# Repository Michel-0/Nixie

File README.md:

# Nixie
All you need to know to build a cold cathode tube display clock

## Concept
There are many different concepts with different features possible.

**The concept of this repository:**

* Controlled by a Raspberry Pi Pico.
* Designed for Gazotron IN-14 tubes, may be adapted for others easily.  
E.g. IN-8 and IN-8-2 should be compatible without any change.
* Makes use of the right comma of the tube, but not the left one.  
However the tube socket PCB connects both to the main PCB.
* Prepared for IN-3 tubes as colon dots.
* Tube voltage step-up boost converter not inclued on this PCB.  
Instead the layout has free space and connectors for it.
* For syncing / keeping time there are 3 options (multiple combinable)
  * **Option A:** A DCF77 (77,5 kHz) radio clock receiver to get the time once powered on.  
Smallest, cheapest and easiest option, but unstable because of many high frequent other things on the board.
  * **Option B:** A RTC (real-time clock) with battery.  
Requires manual time input once or combination with another option.
  * **Option C:** A GPS receiver to get the GPS time once powered on.  
Seems a bit like a overkill, but actually a valid option. Size and costs similar as A & B together.
* Tube driver based on MPSA42 transistors controlled by MCP23008 & MCP23017 connected by I²C to the pico.  
No historical sovjet ICs necessary
* Supplied by external 12V DC.
* Provides connectors for 5V RGB LEDs (e.g. WS2812B).

## Repository
### KiCAD project
Folder `NTC` contains:
* **Main**:  
Clock schematic and PCB
* **Socket**:  
IN-14 schematic and PCB
* **Footprints**  
Project library called `Nixie` containing all used footprints
* **Symbols**  
Project library called `Nixie` containig an additional symbol
* **CAD**  
3D models that weren't included in the default library

### C++ VSCode project
Pico software may or may not be added to this repository in near future.

## Datasheets
[IN-14 Manual](../../wiki/IN‐14-Manuals)

## Dimensioning
[IN-14 Calculations](../../wiki/IN‐14-Calculations)

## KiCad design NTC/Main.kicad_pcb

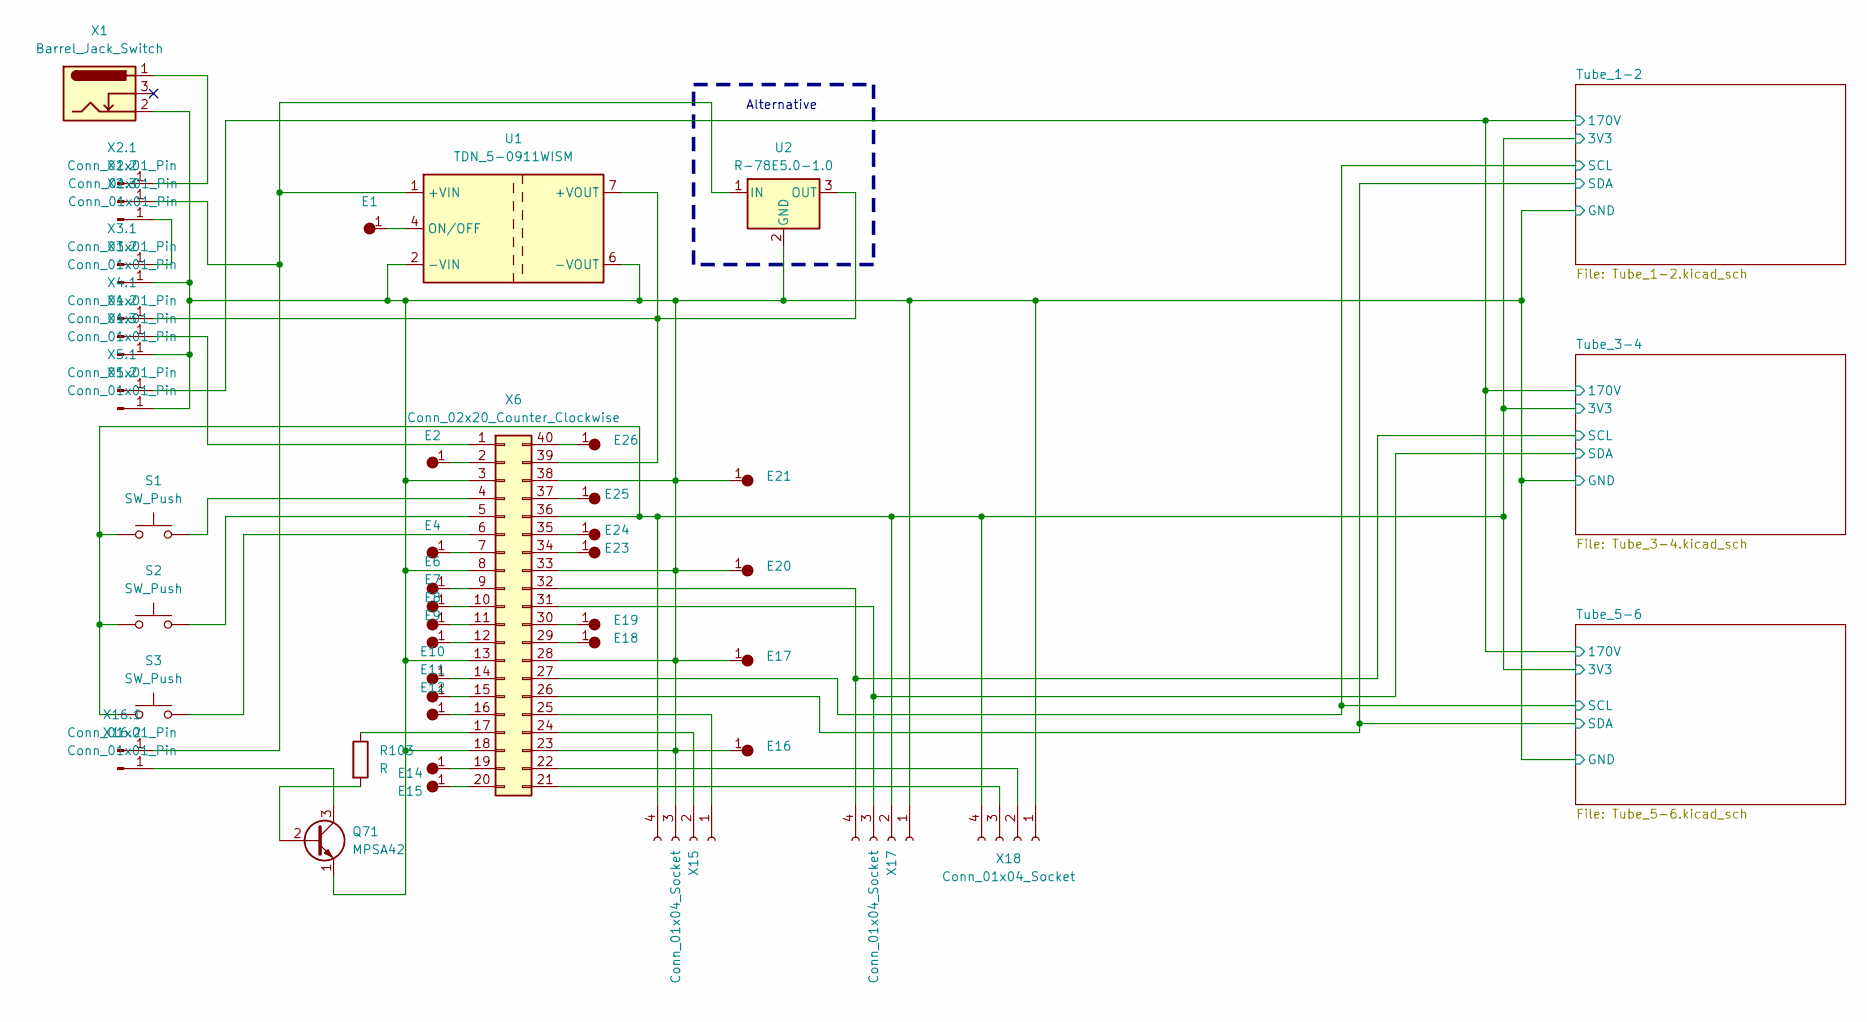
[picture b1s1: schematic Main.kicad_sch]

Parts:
E1, E2, E4, E6, E7, E8, E9, E10, E11, E12, E14, E15, E16, E17, E18, E19, E20, E21, E23, E24, E25, E26: SingleHole
Q71: MPSA42; MPSA-42
R103: R; Resistor-a
S1, S2, S3: SW_Push; Button
U1: TDN_5-0911WISM; DCDC_12V-5V-3W
U2: R-78E5.0-1.0; DCDC_12V-5V-5W
X1: Barrel_Jack_Switch; Socket_5-5
X2.1, X2.2, X2.3, X3.1, X3.2, X4.1, X4.2, X4.3, X5.1, X5.2, X16.1, X16.2: Conn_01x01_Pin; Pin_D1.0mm_L10.0mm
X6: Conn_02x20_Counter_Clockwise; Pinbar_1-20-f
X15: Conn_01x04_Socket; Pinbar_1-4-f-b
X17: Conn_01x04_Socket; Pinbar_1-4-f-c
X18: Conn_01x04_Socket; Pinbar_1-4-f-d

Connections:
/Tube_1-2/3V3: S1.1, S2.1, S3.1, X6.36, X15.4, X17.2, X18.4; also elsewhere on the board
/Tube_1-2/170V: X5.1.1; also elsewhere on the board
/Tube_1-2/GND: E16.1, E17.1, E20.1, E21.1, Q71.1 (E), U1.2 (-VIN), U1.6 (-VOUT), U2.2 (GND), X1.2, X3.2.1, X4.3.1, X5.2.1, X6.3, X6.8, X6.13, X6.18, X6.23, X6.28, X6.33, X6.38, X15.3, X17.1, X18.1; also elsewhere on the board
/Tube_1-2/SCL: X6.27; also elsewhere on the board
/Tube_1-2/SDA: X6.26; also elsewhere on the board
/Tube_3-4/SCL: X6.32, X17.4; also elsewhere on the board
/Tube_3-4/SDA: X6.31, X17.3; also elsewhere on the board
unnamed: Q71.2 (B), R103.2
unnamed: Q71.3 (C), X16.2.1
unnamed: U1.1 (+VIN), U2.1 (IN), X2.2.1, X16.1.1
unnamed: U1.7 (+VOUT), U2.3 (OUT), X4.1.1, X6.39
unnamed: E1.1, U1.4 (ON/OFF)
unnamed: X1.1, X2.1.1
unnamed: X2.3.1, X3.1.1
unnamed: X4.2.1, X6.1
unnamed: E2.1, X6.2
unnamed: S1.2, X6.4
unnamed: S2.2, X6.5
unnamed: S3.2, X6.6
unnamed: E4.1, X6.7
unnamed: E6.1, X6.9
unnamed: E7.1, X6.10
unnamed: E8.1, X6.11
unnamed: E9.1, X6.12
unnamed: E10.1, X6.14
unnamed: E11.1, X6.15
unnamed: E12.1, X6.16
unnamed: R103.1, X6.17
unnamed: E14.1, X6.19
unnamed: E15.1, X6.20
unnamed: E18.1, X6.29
unnamed: E19.1, X6.30
unnamed: E23.1, X6.34
unnamed: E24.1, X6.35
unnamed: E25.1, X6.37
unnamed: E26.1, X6.40
unnamed: X6.25, X15.1
unnamed: X6.24, X15.2
unnamed: X6.22, X18.2
unnamed: X6.21, X18.3

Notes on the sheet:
Alternative

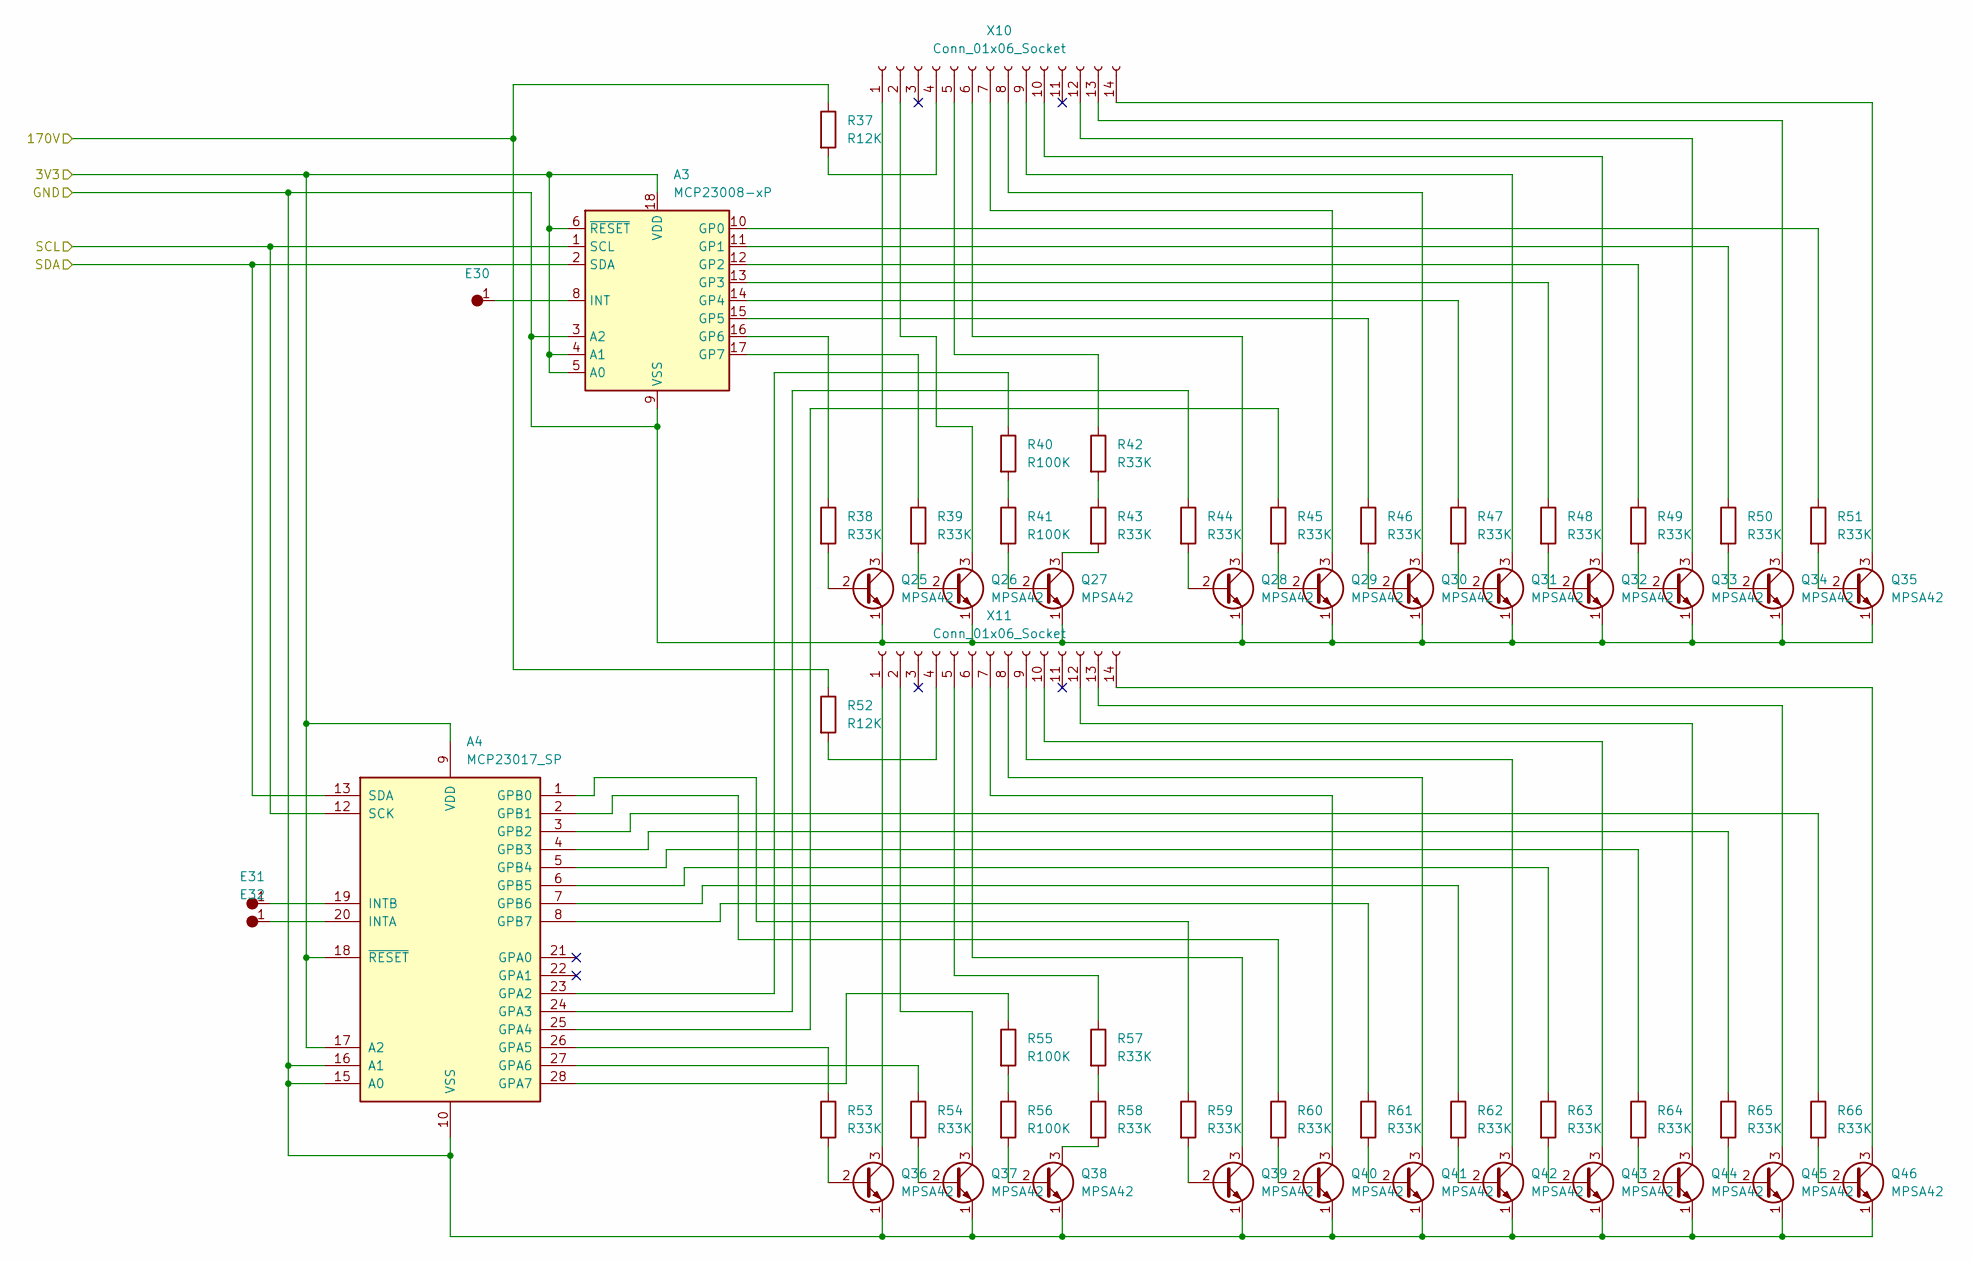
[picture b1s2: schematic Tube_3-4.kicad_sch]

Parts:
A3: MCP23008-xP; DIP-18_IC+Socket
A4: MCP23017_SP; DIP-28_IC+Socket
E30, E31, E32: SingleHole
Q25, Q26, Q27, Q28, Q29, Q30, Q31, Q32, Q33, Q34, Q35, Q36, Q37, Q38, Q39, Q40, Q41, Q42, Q43, Q44, Q45, Q46: MPSA42; MPSA-42
R37, R52: R12K; Resistor-a
R38, R39, R42, R43, R44, R45, R46, R47, R48, R49, R50, R51, R53, R54, R57, R58, R59, R60, R61, R62, R63, R64, R65, R66: R33K; Resistor-a
R40, R41, R55, R56: R100K; Resistor-a
X10, X11: Conn_01x06_Socket; Pinbar_4-14-f

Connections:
/Tube_1-2/3V3: A3.4 (A1), A3.5 (A0), A3.6 (~RESET), A3.18 (VDD), A4.9 (VDD), A4.17 (A2), A4.18 (~RESET); also elsewhere on the board
/Tube_1-2/170V: R37.1, R52.1; also elsewhere on the board
/Tube_1-2/GND: A3.3 (A2), A3.9 (VSS), A4.10 (VSS), A4.15 (A0), A4.16 (A1), Q25.1 (E), Q26.1 (E), Q27.1 (E), Q28.1 (E), Q29.1 (E), Q30.1 (E), Q31.1 (E), Q32.1 (E), Q33.1 (E), Q34.1 (E), Q35.1 (E), Q36.1 (E), Q37.1 (E), Q38.1 (E), Q39.1 (E), Q40.1 (E), Q41.1 (E), Q42.1 (E), Q43.1 (E), Q44.1 (E), Q45.1 (E), Q46.1 (E); also elsewhere on the board
/Tube_3-4/SCL: A3.1 (SCL), A4.12 (SCK); also elsewhere on the board
/Tube_3-4/SDA: A3.2 (SDA), A4.13 (SDA); also elsewhere on the board
unnamed: A3.10 (GP0), R51.1
unnamed: A3.11 (GP1), R50.1
unnamed: A3.12 (GP2), R49.1
unnamed: A3.13 (GP3), R48.1
unnamed: A3.14 (GP4), R47.1
unnamed: A3.15 (GP5), R46.1
unnamed: A3.16 (GP6), R38.1
unnamed: A3.17 (GP7), R39.1
unnamed: A3.8 (INT), E30.1
unnamed: A4.23 (GPA2), R40.1
unnamed: A4.24 (GPA3), R44.1
unnamed: A4.25 (GPA4), R45.1
unnamed: A4.26 (GPA5), R53.1
unnamed: A4.27 (GPA6), R54.1
unnamed: A4.28 (GPA7), R55.1
unnamed: A4.1 (GPB0), R59.1
unnamed: A4.2 (GPB1), R60.1
unnamed: A4.3 (GPB2), R66.1
unnamed: A4.4 (GPB3), R65.1
unnamed: A4.5 (GPB4), R64.1
unnamed: A4.6 (GPB5), R63.1
unnamed: A4.7 (GPB6), R62.1
unnamed: A4.8 (GPB7), R61.1
unnamed: A4.20 (INTA), E32.1
unnamed: A4.19 (INTB), E31.1
unnamed: Q25.2 (B), R38.2
unnamed: Q25.3 (C), X10.1
unnamed: Q26.2 (B), R39.2
unnamed: Q26.3 (C), X10.2
unnamed: Q27.2 (B), R41.2
unnamed: Q27.3 (C), R43.2
unnamed: Q28.2 (B), R44.2
unnamed: Q28.3 (C), X10.6
unnamed: Q29.2 (B), R45.2
unnamed: Q29.3 (C), X10.7
unnamed: Q30.2 (B), R46.2
unnamed: Q30.3 (C), X10.8
unnamed: Q31.2 (B), R47.2
unnamed: Q31.3 (C), X10.9
unnamed: Q32.2 (B), R48.2
unnamed: Q32.3 (C), X10.10
unnamed: Q33.2 (B), R49.2
unnamed: Q33.3 (C), X10.12
unnamed: Q34.2 (B), R50.2
unnamed: Q34.3 (C), X10.13
unnamed: Q35.2 (B), R51.2
unnamed: Q35.3 (C), X10.14
unnamed: Q36.2 (B), R53.2
unnamed: Q36.3 (C), X11.1
unnamed: Q37.2 (B), R54.2
unnamed: Q37.3 (C), X11.2
unnamed: Q38.2 (B), R56.2
unnamed: Q38.3 (C), R58.2
unnamed: Q39.2 (B), R59.2
unnamed: Q39.3 (C), X11.6
unnamed: Q40.2 (B), R60.2
unnamed: Q40.3 (C), X11.7
unnamed: Q41.2 (B), R61.2
unnamed: Q41.3 (C), X11.8
unnamed: Q42.2 (B), R62.2
unnamed: Q42.3 (C), X11.9
unnamed: Q43.2 (B), R63.2
unnamed: Q43.3 (C), X11.10
unnamed: Q44.2 (B), R64.2
unnamed: Q44.3 (C), X11.12
unnamed: Q45.2 (B), R65.2
unnamed: Q45.3 (C), X11.13
unnamed: Q46.2 (B), R66.2
unnamed: Q46.3 (C), X11.14
unnamed: R40.2, R41.1
unnamed: R42.2, R43.1
unnamed: R55.2, R56.1
unnamed: R57.2, R58.1
unnamed: R37.2, X10.4
unnamed: R42.1, X10.5
unnamed: R52.2, X11.4
unnamed: R57.1, X11.5

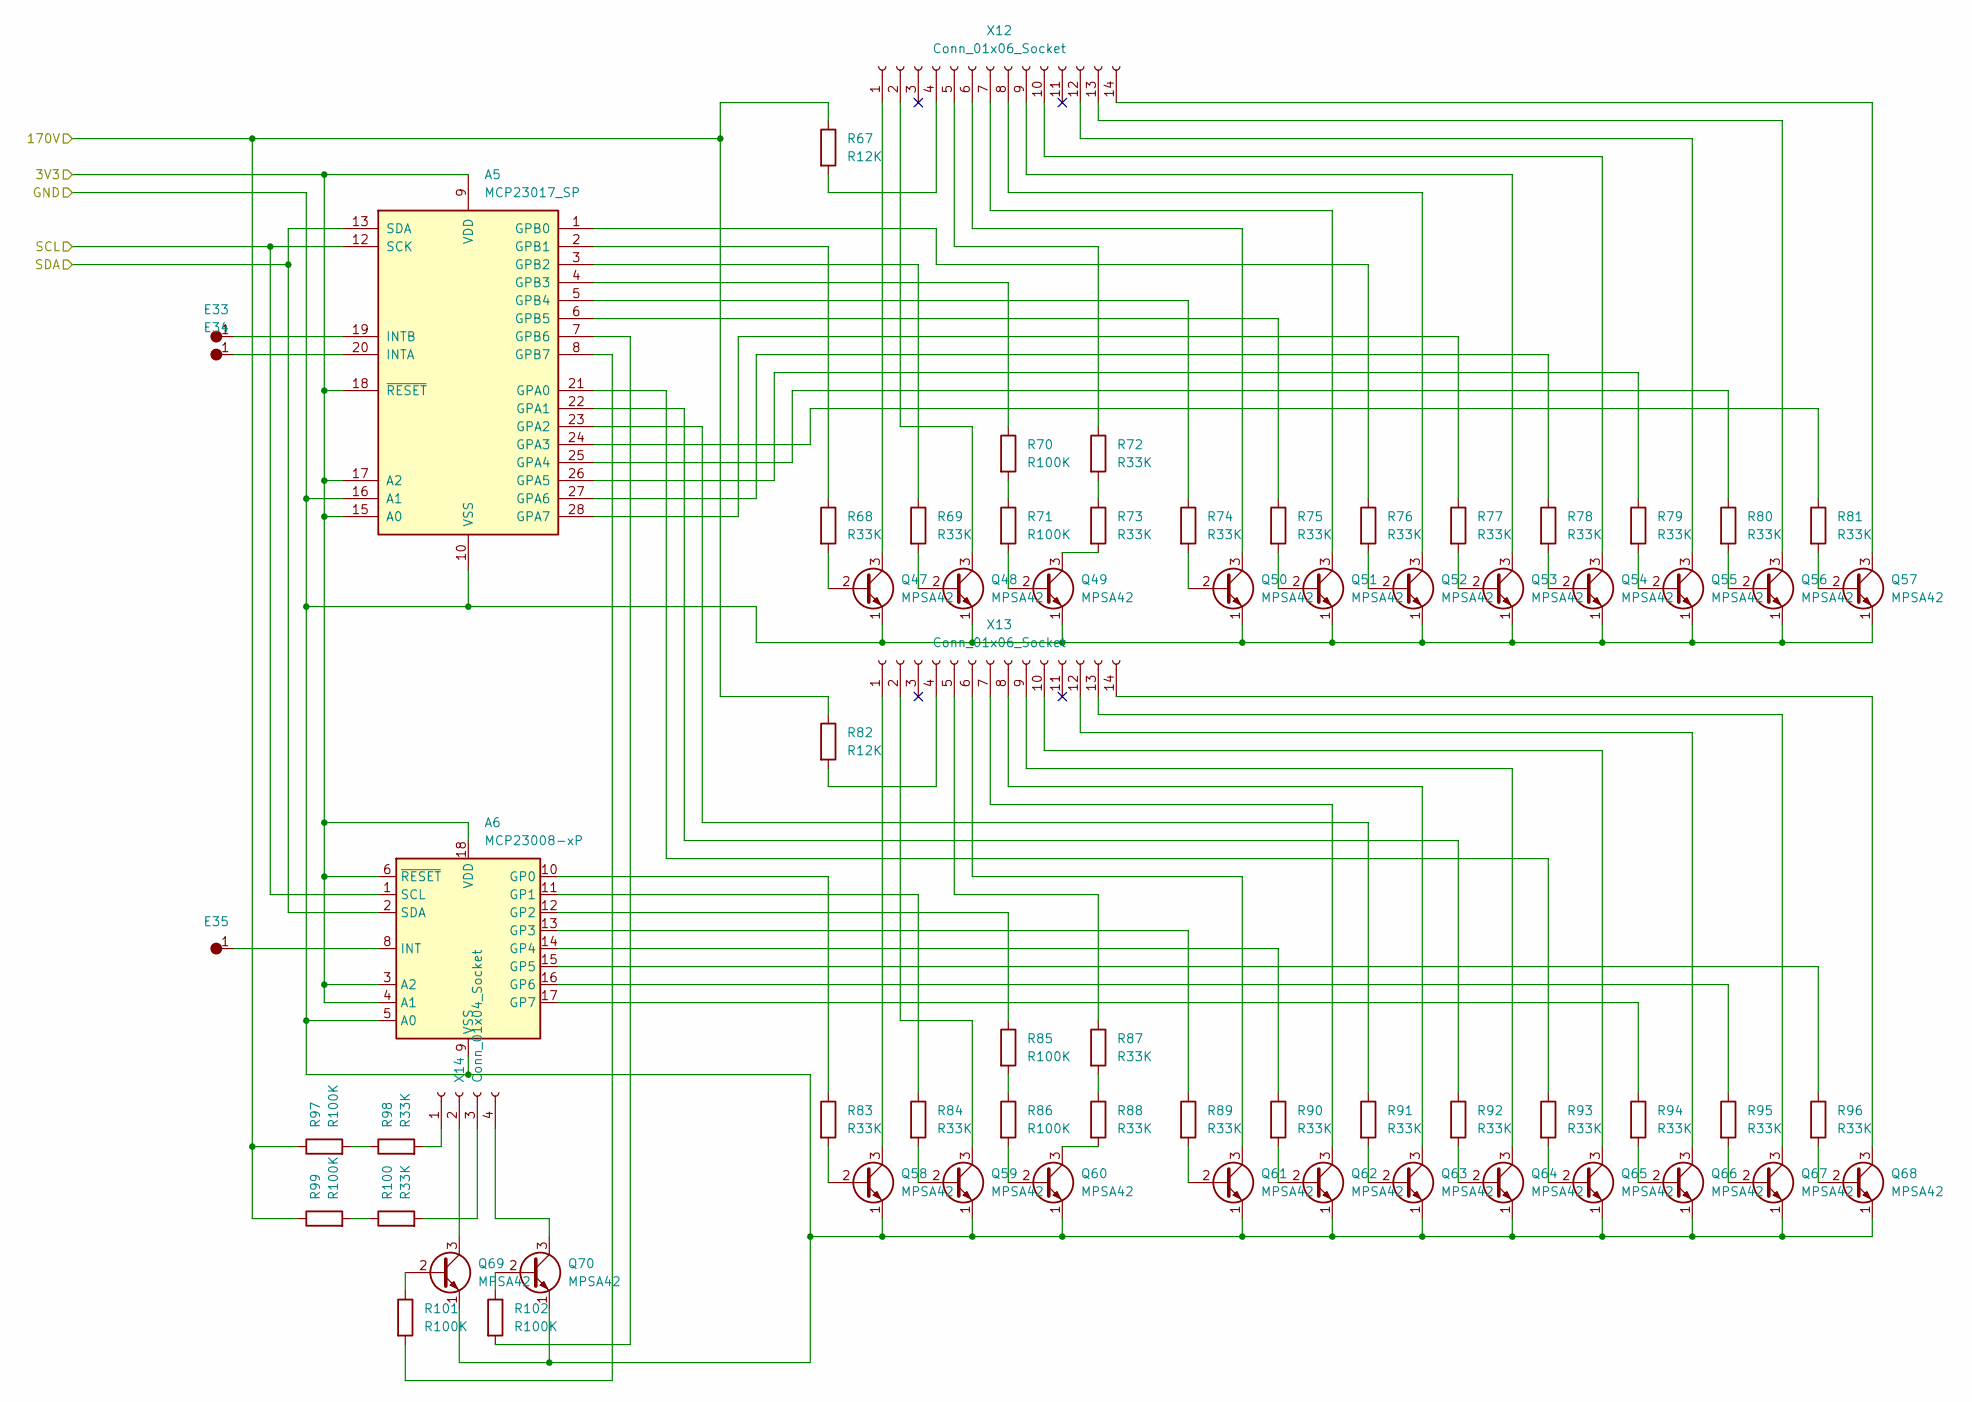
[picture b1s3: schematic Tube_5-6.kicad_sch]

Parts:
A5: MCP23017_SP; DIP-28_IC+Socket
A6: MCP23008-xP; DIP-18_IC+Socket
E33, E34, E35: SingleHole
Q47, Q48, Q49, Q50, Q51, Q52, Q53, Q54, Q55, Q56, Q57, Q58, Q59, Q60, Q61, Q62, Q63, Q64, Q65, Q66, Q67, Q68, Q69, Q70: MPSA42; MPSA-42
R67, R82: R12K; Resistor-a
R68, R69, R72, R73, R74, R75, R76, R77, R78, R79, R80, R81, R83, R84, R87, R88, R89, R90, R91, R92, R93, R94, R95, R96, R98, R100: R33K; Resistor-a
R70, R71, R85, R86, R97, R99, R101, R102: R100K; Resistor-a
X12, X13: Conn_01x06_Socket; Pinbar_4-14-f
X14: Conn_01x04_Socket; Pinbar_1-4-f-a

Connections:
/Tube_1-2/3V3: A5.9 (VDD), A5.15 (A0), A5.17 (A2), A5.18 (~RESET), A6.3 (A2), A6.4 (A1), A6.6 (~RESET), A6.18 (VDD); also elsewhere on the board
/Tube_1-2/170V: R67.1, R82.1, R97.1, R99.1; also elsewhere on the board
/Tube_1-2/GND: A5.10 (VSS), A5.16 (A1), A6.5 (A0), A6.9 (VSS), Q47.1 (E), Q48.1 (E), Q49.1 (E), Q50.1 (E), Q51.1 (E), Q52.1 (E), Q53.1 (E), Q54.1 (E), Q55.1 (E), Q56.1 (E), Q57.1 (E), Q58.1 (E), Q59.1 (E), Q60.1 (E), Q61.1 (E), Q62.1 (E), Q63.1 (E), Q64.1 (E), Q65.1 (E), Q66.1 (E), Q67.1 (E), Q68.1 (E), Q69.1 (E), Q70.1 (E); also elsewhere on the board
/Tube_1-2/SCL: A5.12 (SCK), A6.1 (SCL); also elsewhere on the board
/Tube_1-2/SDA: A5.13 (SDA), A6.2 (SDA); also elsewhere on the board
unnamed: A5.21 (GPA0), R93.1
unnamed: A5.22 (GPA1), R92.1
unnamed: A5.23 (GPA2), R91.1
unnamed: A5.24 (GPA3), R81.1
unnamed: A5.25 (GPA4), R80.1
unnamed: A5.26 (GPA5), R79.1
unnamed: A5.27 (GPA6), R78.1
unnamed: A5.28 (GPA7), R77.1
unnamed: A5.1 (GPB0), R76.1
unnamed: A5.2 (GPB1), R68.1
unnamed: A5.3 (GPB2), R69.1
unnamed: A5.4 (GPB3), R70.1
unnamed: A5.5 (GPB4), R74.1
unnamed: A5.6 (GPB5), R75.1
unnamed: A5.7 (GPB6), R102.2
unnamed: A5.8 (GPB7), R101.2
unnamed: A5.20 (INTA), E34.1
unnamed: A5.19 (INTB), E33.1
unnamed: A6.10 (GP0), R83.1
unnamed: A6.11 (GP1), R84.1
unnamed: A6.12 (GP2), R85.1
unnamed: A6.13 (GP3), R89.1
unnamed: A6.14 (GP4), R90.1
unnamed: A6.15 (GP5), R96.1
unnamed: A6.16 (GP6), R95.1
unnamed: A6.17 (GP7), R94.1
unnamed: A6.8 (INT), E35.1
unnamed: Q47.2 (B), R68.2
unnamed: Q47.3 (C), X12.1
unnamed: Q48.2 (B), R69.2
unnamed: Q48.3 (C), X12.2
unnamed: Q49.2 (B), R71.2
unnamed: Q49.3 (C), R73.2
unnamed: Q50.2 (B), R74.2
unnamed: Q50.3 (C), X12.6
unnamed: Q51.2 (B), R75.2
unnamed: Q51.3 (C), X12.7
unnamed: Q52.2 (B), R76.2
unnamed: Q52.3 (C), X12.8
unnamed: Q53.2 (B), R77.2
unnamed: Q53.3 (C), X12.9
unnamed: Q54.2 (B), R78.2
unnamed: Q54.3 (C), X12.10
unnamed: Q55.2 (B), R79.2
unnamed: Q55.3 (C), X12.12
unnamed: Q56.2 (B), R80.2
unnamed: Q56.3 (C), X12.13
unnamed: Q57.2 (B), R81.2
unnamed: Q57.3 (C), X12.14
unnamed: Q58.2 (B), R83.2
unnamed: Q58.3 (C), X13.1
unnamed: Q59.2 (B), R84.2
unnamed: Q59.3 (C), X13.2
unnamed: Q60.2 (B), R86.2
unnamed: Q60.3 (C), R88.2
unnamed: Q61.2 (B), R89.2
unnamed: Q61.3 (C), X13.6
unnamed: Q62.2 (B), R90.2
unnamed: Q62.3 (C), X13.7
unnamed: Q63.2 (B), R91.2
unnamed: Q63.3 (C), X13.8
unnamed: Q64.2 (B), R92.2
unnamed: Q64.3 (C), X13.9
unnamed: Q65.2 (B), R93.2
unnamed: Q65.3 (C), X13.10
unnamed: Q66.2 (B), R94.2
unnamed: Q66.3 (C), X13.12
unnamed: Q67.2 (B), R95.2
unnamed: Q67.3 (C), X13.13
unnamed: Q68.2 (B), R96.2
unnamed: Q68.3 (C), X13.14
unnamed: Q69.2 (B), R101.1
unnamed: Q69.3 (C), X14.2
unnamed: Q70.2 (B), R102.1
unnamed: Q70.3 (C), X14.4
unnamed: R70.2, R71.1
unnamed: R72.2, R73.1
unnamed: R85.2, R86.1
unnamed: R87.2, R88.1
unnamed: R97.2, R98.1
unnamed: R99.2, R100.1
unnamed: R67.2, X12.4
unnamed: R72.1, X12.5
unnamed: R82.2, X13.4
unnamed: R87.1, X13.5
unnamed: R98.2, X14.1
unnamed: R100.2, X14.3

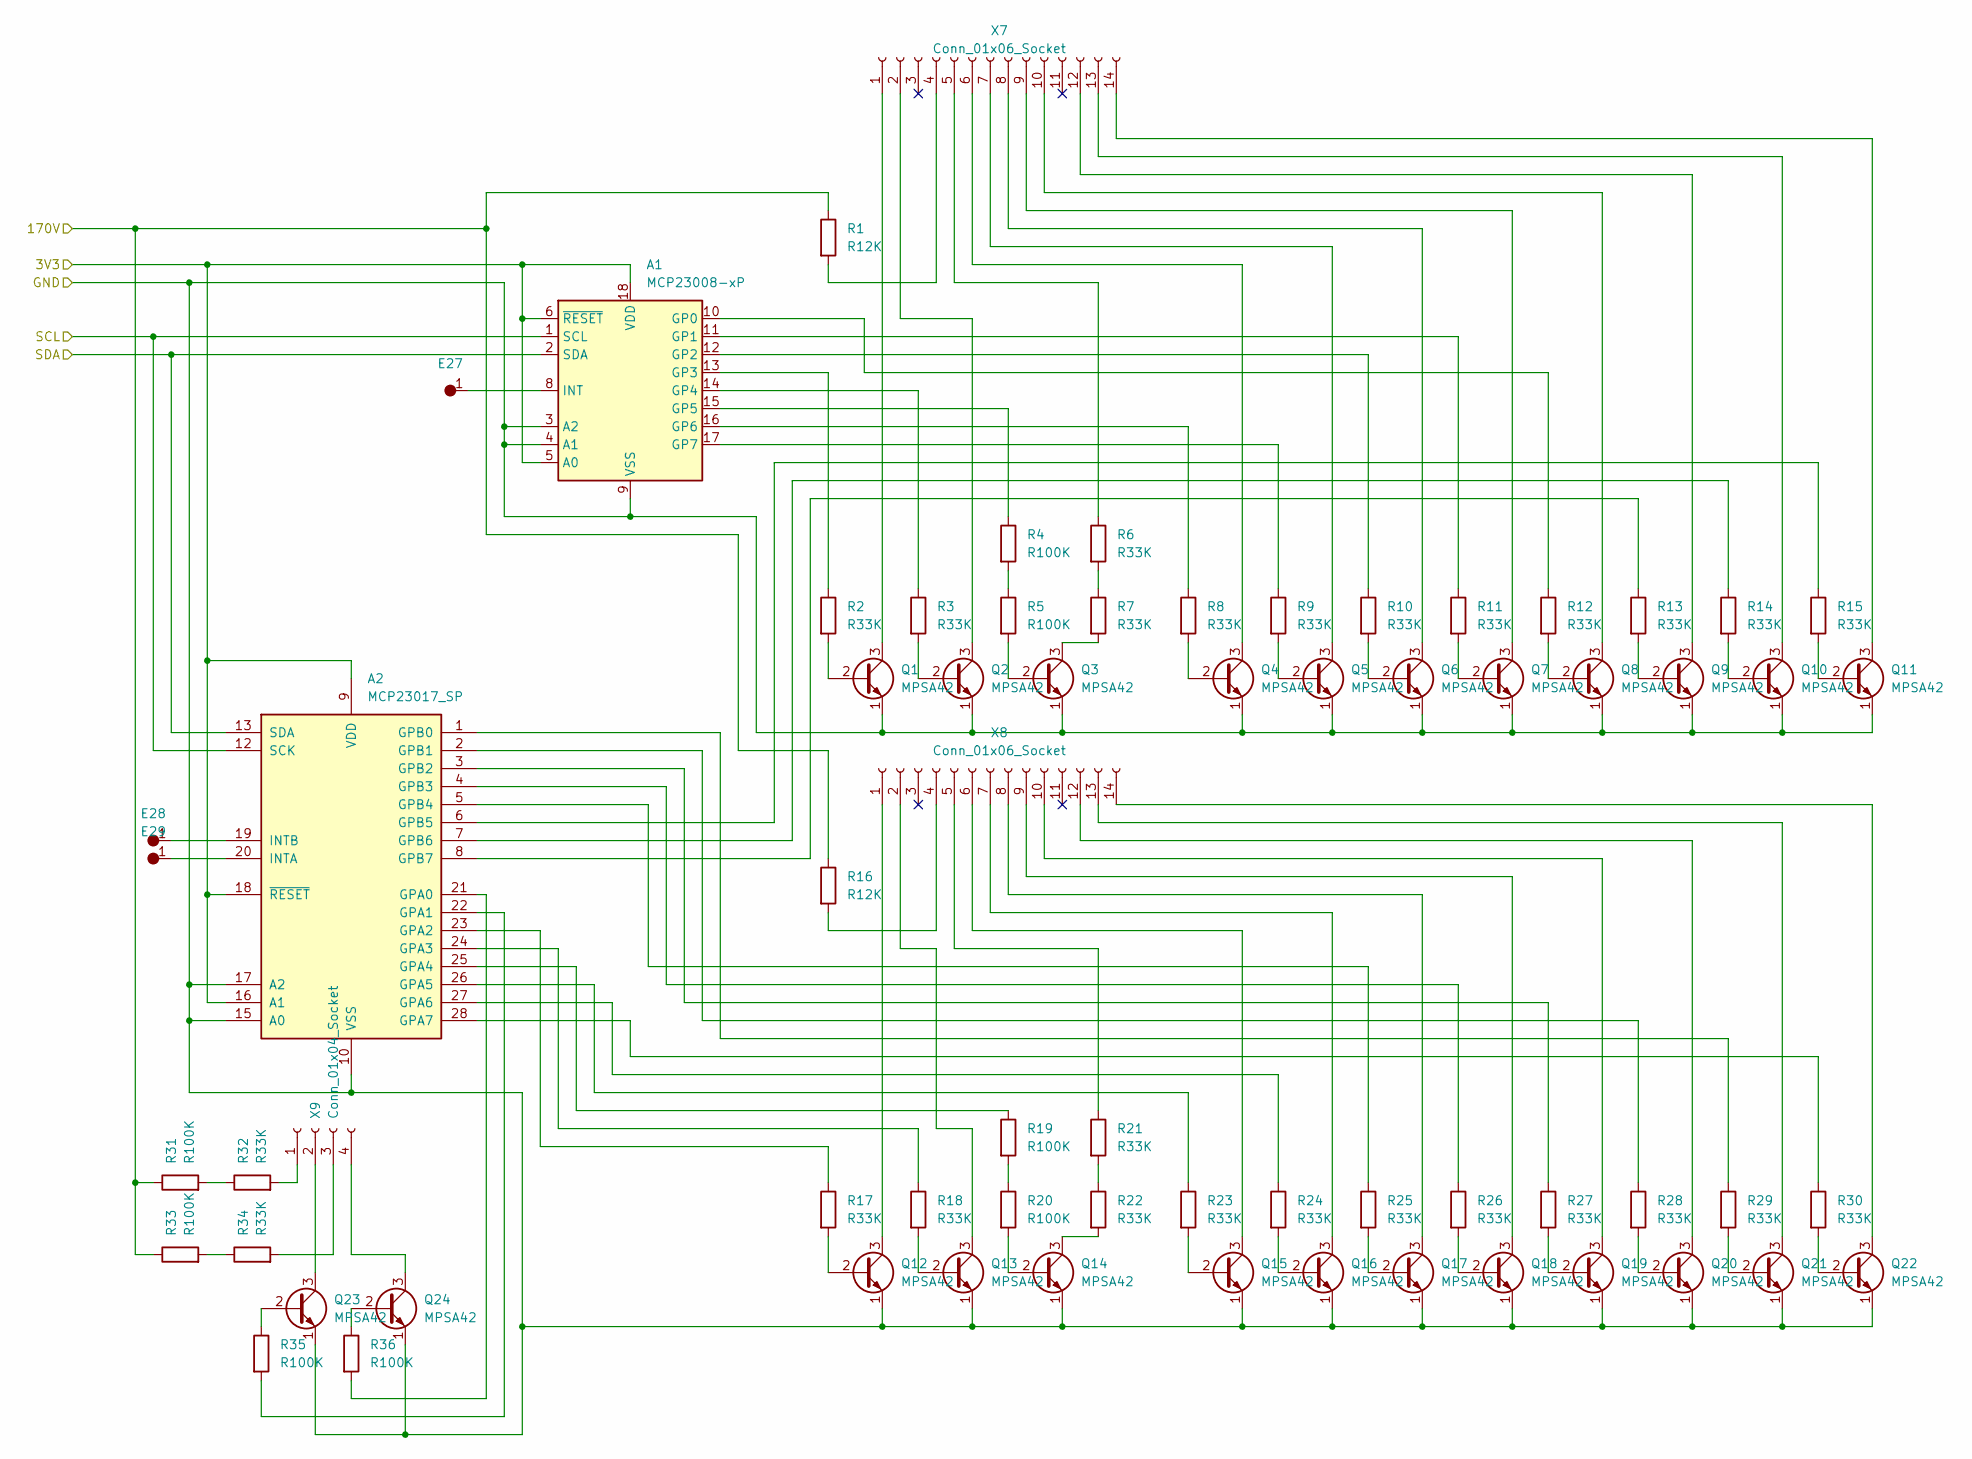
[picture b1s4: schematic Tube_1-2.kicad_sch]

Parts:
A1: MCP23008-xP; DIP-18_IC+Socket
A2: MCP23017_SP; DIP-28_IC+Socket
E27, E28, E29: SingleHole
Q1, Q2, Q3, Q4, Q5, Q6, Q7, Q8, Q9, Q10, Q11, Q12, Q13, Q14, Q15, Q16, Q17, Q18, Q19, Q20, Q21, Q22, Q23, Q24: MPSA42; MPSA-42
R1, R16: R12K; Resistor-a
R2, R3, R6, R7, R8, R9, R10, R11, R12, R13, R14, R15, R17, R18, R21, R22, R23, R24, R25, R26, R27, R28, R29, R30, R32, R34: R33K; Resistor-a
R4, R5, R19, R20, R31, R33, R35, R36: R100K; Resistor-a
X7, X8: Conn_01x06_Socket; Pinbar_4-14-f
X9: Conn_01x04_Socket; Pinbar_1-4-f-a

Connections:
/Tube_1-2/3V3: A1.5 (A0), A1.6 (~RESET), A1.18 (VDD), A2.9 (VDD), A2.16 (A1), A2.18 (~RESET); also elsewhere on the board
/Tube_1-2/170V: R1.1, R16.1, R31.1, R33.1; also elsewhere on the board
/Tube_1-2/GND: A1.3 (A2), A1.4 (A1), A1.9 (VSS), A2.10 (VSS), A2.15 (A0), A2.17 (A2), Q1.1 (E), Q2.1 (E), Q3.1 (E), Q4.1 (E), Q5.1 (E), Q6.1 (E), Q7.1 (E), Q8.1 (E), Q9.1 (E), Q10.1 (E), Q11.1 (E), Q12.1 (E), Q13.1 (E), Q14.1 (E), Q15.1 (E), Q16.1 (E), Q17.1 (E), Q18.1 (E), Q19.1 (E), Q20.1 (E), Q21.1 (E), Q22.1 (E), Q23.1 (E), Q24.1 (E); also elsewhere on the board
/Tube_1-2/SCL: A1.1 (SCL), A2.12 (SCK); also elsewhere on the board
/Tube_1-2/SDA: A1.2 (SDA), A2.13 (SDA); also elsewhere on the board
unnamed: A1.10 (GP0), R12.1
unnamed: A1.11 (GP1), R11.1
unnamed: A1.12 (GP2), R10.1
unnamed: A1.13 (GP3), R2.1
unnamed: A1.14 (GP4), R3.1
unnamed: A1.15 (GP5), R4.1
unnamed: A1.16 (GP6), R8.1
unnamed: A1.17 (GP7), R9.1
unnamed: A1.8 (INT), E27.1
unnamed: A2.21 (GPA0), R36.2
unnamed: A2.22 (GPA1), R35.2
unnamed: A2.23 (GPA2), R17.1
unnamed: A2.24 (GPA3), R18.1
unnamed: A2.25 (GPA4), R19.1
unnamed: A2.26 (GPA5), R23.1
unnamed: A2.27 (GPA6), R24.1
unnamed: A2.28 (GPA7), R30.1
unnamed: A2.1 (GPB0), R29.1
unnamed: A2.2 (GPB1), R28.1
unnamed: A2.3 (GPB2), R27.1
unnamed: A2.4 (GPB3), R26.1
unnamed: A2.5 (GPB4), R25.1
unnamed: A2.6 (GPB5), R15.1
unnamed: A2.7 (GPB6), R14.1
unnamed: A2.8 (GPB7), R13.1
unnamed: A2.20 (INTA), E29.1
unnamed: A2.19 (INTB), E28.1
unnamed: Q1.2 (B), R2.2
unnamed: Q1.3 (C), X7.1
unnamed: Q2.2 (B), R3.2
unnamed: Q2.3 (C), X7.2
unnamed: Q3.2 (B), R5.2
unnamed: Q3.3 (C), R7.2
unnamed: Q4.2 (B), R8.2
unnamed: Q4.3 (C), X7.6
unnamed: Q5.2 (B), R9.2
unnamed: Q5.3 (C), X7.7
unnamed: Q6.2 (B), R10.2
unnamed: Q6.3 (C), X7.8
unnamed: Q7.2 (B), R11.2
unnamed: Q7.3 (C), X7.9
unnamed: Q8.2 (B), R12.2
unnamed: Q8.3 (C), X7.10
unnamed: Q9.2 (B), R13.2
unnamed: Q9.3 (C), X7.12
unnamed: Q10.2 (B), R14.2
unnamed: Q10.3 (C), X7.13
unnamed: Q11.2 (B), R15.2
unnamed: Q11.3 (C), X7.14
unnamed: Q12.2 (B), R17.2
unnamed: Q12.3 (C), X8.1
unnamed: Q13.2 (B), R18.2
unnamed: Q13.3 (C), X8.2
unnamed: Q14.2 (B), R20.2
unnamed: Q14.3 (C), R22.2
unnamed: Q15.2 (B), R23.2
unnamed: Q15.3 (C), X8.6
unnamed: Q16.2 (B), R24.2
unnamed: Q16.3 (C), X8.7
unnamed: Q17.2 (B), R25.2
unnamed: Q17.3 (C), X8.8
unnamed: Q18.2 (B), R26.2
unnamed: Q18.3 (C), X8.9
unnamed: Q19.2 (B), R27.2
unnamed: Q19.3 (C), X8.10
unnamed: Q20.2 (B), R28.2
unnamed: Q20.3 (C), X8.12
unnamed: Q21.2 (B), R29.2
unnamed: Q21.3 (C), X8.13
unnamed: Q22.2 (B), R30.2
unnamed: Q22.3 (C), X8.14
unnamed: Q23.2 (B), R35.1
unnamed: Q23.3 (C), X9.2
unnamed: Q24.2 (B), R36.1
unnamed: Q24.3 (C), X9.4
unnamed: R4.2, R5.1
unnamed: R6.2, R7.1
unnamed: R19.2, R20.1
unnamed: R21.2, R22.1
unnamed: R31.2, R32.1
unnamed: R33.2, R34.1
unnamed: R1.2, X7.4
unnamed: R6.1, X7.5
unnamed: R16.2, X8.4
unnamed: R21.1, X8.5
unnamed: R32.2, X9.1
unnamed: R34.2, X9.3

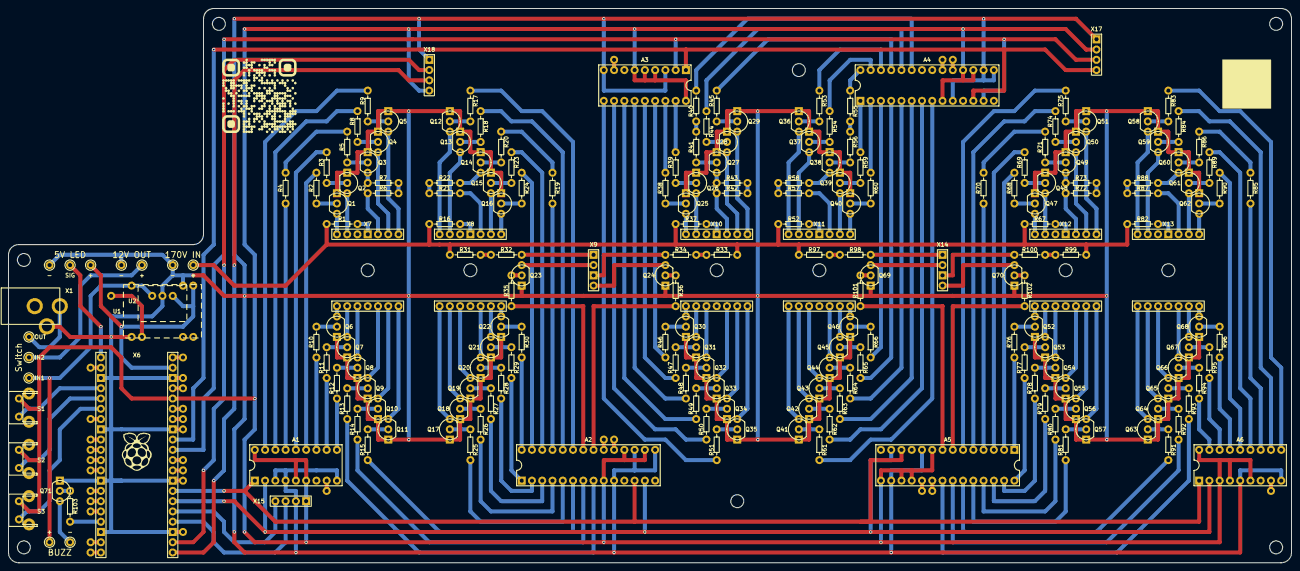
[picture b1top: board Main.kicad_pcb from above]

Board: 2 copper layers, 317.5 x 137.2 mm, 241 parts (0 on the bottom side), 291 nets.

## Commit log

2025-01-01 Added KiCAD project
2025-01-01 Added QR
2025-01-02 added soldermask expansion
2025-01-02 Added LICENSE
2025-01-03 Added alternative DC/DC converter and Tube schematic
2025-01-06 Changed to 14pin socket
2025-01-06 added DMC
2025-01-15 Added GPS
